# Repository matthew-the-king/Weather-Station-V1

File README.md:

# Weather-Station-V1
The Weather Station V1 is a Solar- and Battery-powered Weather Station that measures humidity, pressure, temperature, and air quality, and sends all data over Wi-Fi for a client to receive or records it to an SD card.

## |FEATURES IN DEPTH|<br>
The Weather Station V1 uses multiple sensors to collect data; here is the list:<br>
1.STS40-AD1B-R3(Temperature Sensor)<br>
2.BMP581(Pressure Sensor)<br>
3.ENS160-BGLT(Air qaulity Sensor)<br>
4.SAM-M10Q-00B(GPS IC)<br>
To view the data the Weather Station V1 collects, the PCB has an SD card slot that records data over long periods and an ESP32-C3 that can send data over WiFi.<br>

<br>
The Weather Station V1 can be powered with a solar panel. To hook up the solar panel, connect the power wires with the correct polarity to the blue screw-in terminal. Here is the [link](https://www.amazon.com/ECO-WORTHY-Monocrystalline-Waterproof-Charging-Applications/dp/B01IFJ73X4/ref=sr_1_4?crid=3QHAHQSNMHFSL&dib=eyJ2IjoiMSJ9.NCFwgk3sAcXWyB454Pk5SPNcQemk34eTFudncpU4z0kJxmG-NXfIaFsG7l4m57yuxXUE0gBqu5lgGJoBbALUTFjF2K6-mGWYJWMwcwzsFfhhP3rzPJ4SUP1idMQb-H-VBpm4El9aRgOr08ZAze0ncVoFDJLv6Px1nW_MmPlfGzO2yde_wccv_r7rToX8MT91kRBLzjtbjo7iDcouW79qZ-3ntSCusWl1HjOpdd0R_DA.tXCmzJyMkYVnmj8B4maCWZT6sQgtKzylotzIh5rUZ2Y&dib_tag=se&keywords=solar%2Bpanels&qid=1789531833&refinements=p_36%3A-3800&rnid=2661611011&sprefix=solar%2Bpanels%2Caps%2C245&sr=8-4&th=1), it cost around $29(As of october 10, 2026), to the Solar panel I am using; any Solar panel that can supply over 2 amps and more than 20 volts will work.<br>
<br>
<br>
The Weather Station V1 features an LTC4162, which is a LiFePO4 battery step-down charger with a Power path. To set up the cell count properly, JP1 and JP4 must be bridged. 
The PCB includes a port for soldering a thermistor for battery protection.

The current configuration of the PCB requires 4 LiFePO4 batteries(https://www.digikey.com/en/products/detail/zeus-battery-products/PCIFR18650-1500/9828824)
The PCB has THT 18650 Battery holder footprint on the bottom side of the board, allowing for quick and easy connection of batteries to the PCB.<br>
<br>
The board has a USB-C port for each MCU to make programming as easy as possible, but in case the user does not want to use USB programming, there are also header pins on the other side of the
board that allow for ESP32 UART programming and STM32 serial wire debug and programming.<br>

<br>
## |PRODUCTION|<br>
To produce the PCB, use your preferred PCB manufacturer (PCBway, JLCPCB, etc.).  The Bill of Materials is listed here:<br>
* If Digi-Key does not have the part stocked, check other vendors like Mouser. <br>
*Prices as of October 10, 2026<br>

| Designator | Footprint | Qty | Value / Part | Part Link |Price|
|---|---|---:|---|---|---|
| BT5 | BAT_BK-18650-PC8 | 1 | BK-18650-PC8 | [Link](https://www.digikey.com/en/products/detail/mpd-memory-protection-devices/BK-18650-PC8/2330515)|$6.22|
| C1 | 0603 | 1 | 330nF | [Link](https://www.digikey.com/en/products/detail/tdk/CGA3E3X7R1H334K080AB/4931465)|$0.26|
| C10, C27, C3, C38, C39, C4, C40, C41, C45, C46, C5, C50, C51, C52, C53, C54, C6, C62, C63, C64, C9 | 0402 | 21 | 0.1uF |[Link](https://www.digikey.com/en/products/detail/samsung-electro-mechanics/CL05A104KA5NNNC/3886701?s=N4IgTCBcDaIMIBkAMBWAggRiQFgNJpQDli4QBdAXyA) | $0.38|
| C11, C37, C44, C57, C65 | 0402 | 5 | 10uF |[Link](https://www.digikey.com/en/products/detail/murata-electronics/GRM155R60J106ME15D/5877401) |$0.85|
| C12, C13, C16, C42, C43, C61, C66 | 0402 | 7 | 1uF |[Link](https://www.digikey.com/en/products/detail/samsung-electro-mechanics/CL05A105KO5NNNC/3886725) |$0.70|
| C14 | 0402 | 1 | 22nF |[Link](https://www.digikey.com/en/products/detail/murata-electronics/GRM155R71H223KA12D/965898) |$0.11|
| C15, C18, C2, C24, C26, C7 | 1210 | 6 | 10uF |[Link](https://www.digikey.com/en/products/detail/murata-electronics/GCJ32EC71H106KA01K/9867929) |$7.08|
| C17, C22, C23, C29, C60, C67, C68, C69 | 0603 | 8 | 0.1uF |[Link](https://www.digikey.com/en/products/detail/kemet/C0603C104K5RACTU/1465594)|$1.12|
| C25, C28 | CAP_EEH-ZA1V151P_PAN | 2 | 150uF |[Link](https://www.digikey.com/en/products/detail/panasonic-industry/EEH-ZA1V151P/3088122) |$3.52|
| C34, C35, C36 | 0805 | 3 | 220nF |[Link](https://www.digikey.com/en/products/detail/kemet/C0805C224K5RACTU/754753) |$0.93|
| C47, C48 | 0201 | 2 | C |Will Post link when Done with testing||
| C49 | 0603 | 1 | 4.7uF |[Link](https://www.digikey.com/en/products/detail/murata-electronics/GRM188R61E475KE11D/3900465) |$0.24|
| C55, C8 | 0603 | 2 | 22uF |[Link](https://www.digikey.com/en/products/detail/holy-stone-enterprise-co-ltd/C0603B226M010T/16895513) |$0.68|
| C56 | WCAP-PSHP_8X8.7_DXL_ | 1 | 470uF |[Link](https://www.digikey.com/en/products/detail/w%C3%BCrth-elektronik/875115252003/5147615) |$1.32|
| C58 | 0402 | 1 | 470pF |[Link](https://www.digikey.com/en/products/detail/murata-electronics/GRM1555C1H471JA01D/587210) |$0.10|
| C59 | 0402 | 1 | 100pF |[Link](https://www.digikey.com/en/products/detail/murata-electronics/GRM1555C1H101JA01D/3693829) |$0.11|
| D1, D5, D6 | D_SOD-123F | 3 | 40V |[Link](https://www.digikey.com/en/products/detail/smc-diode-solutions/DSS14U/8341859) |$0.63|
| D2 | D_SMA | 1 | D |[Link](https://www.digikey.com/en/products/detail/mcc-micro-commercial-components/SK310A-LTP/2642015) |$0.52|
| D3 | D_SOD-123 | 1 | Zener 16V |[Link](https://www.digikey.com/en/products/detail/diodes-incorporated/DDZ9703-7/5218356) |$0.36|
| D4 | D_SMA | 1 | 100V |[Link](https://www.digikey.com/en/products/detail/mcc-micro-commercial-components/SK310A-LTP/2642015) |$0.52|
| ESP32_USB1, STM32_USB1 | SAMESKY_UJ20-C-H-G-SMT-P16-TR | 2 | UJ20-C-H-G-SMT-1-P16-TR |[Link](https://www.digikey.com/en/products/detail/same-sky-formerly-cui-devices/UJ20-C-H-G-SMT-P16-TR/24818595) |$1.30|
| FB1, FB2 | 0603 | 2 | 120R |[Link](https://www.digikey.com/en/products/detail/pulse-electronics/PE-0603PFB121ST/5050544) |$0.20|
| J1 | GCT_MEM2075-00-140-01-A | 1 | MEM2075-00-140-01-A |[Link](https://www.digikey.com/en/products/detail/gct/MEM2075-00-140-01-A/9859614) |$1.92|
| J2 | TE_CONREVSMA002 | 1 | CONREVSMA002 |[Link](https://www.digikey.com/en/products/detail/te-connectivity-linx/CONREVSMA002/340145) |$2.78|
| J3 | PinHeader_1x05_P2.54mm_Vertical | 1 | Conn_01x05_Pin |2.54mm Male Header Pins|
| J4 | PinHeader_1x04_P2.54mm_Vertical | 1 | Conn_01x04_Pin |2.54mm Male Header Pins|
| J5 | OST_OSTTC020162 | 1 | Solar Panel |[Link](https://www.digikey.com/en/products/detail/on-shore-technology-inc/OSTTC020162/614549?s=N4IgTCBcDaIPIGUAqSDCAGM6CMA2CAugL5A) | $0.62|
| JP8, JP9 | PinSocket_1x02_P2.54mm_Vertical | 2 | Jumper_2_Open |2.54mm Male Header Pins|
| L1 | IND_PA4342.402NLT | 1 | 4uH |[Link](https://www.digikey.com/en/products/detail/pulse-electronics/PA4342-402NLT/5641799) |$1.16|
| L2 | 0201 | 1 | L |Will Post link when Done with testing||
| L3 | 1008 | 1 | 1.5uH |[Link](https://www.digikey.com/en/products/detail/murata-electronics/DFE252012P-1R5M-P2/5247259) |$0.22|
| Q10, Q9 | NPNBEC_SOT-23_OSI | 2 | BSR14 |[Link](https://www.digikey.com/en/products/detail/onsemi/BSR14/965251) |$0.96|
| Q11, Q14 | WDFN8_511DR_OSI-L | 2 | FDMC8327L |[Link](https://www.digikey.com/en/products/detail/onsemi/FDMC8327L/4314821?curr=usd&utm_campaign=buynow&utm_medium=aggregator&utm_source=octopart) |$3.00|
| Q3, Q4, Q5, Q6 | TDSON-8-1 | 4 | CSD18534Q5A |[Link](https://www.digikey.com/en/products/detail/texas-instruments/CSD18534Q5A/3830016) |$6.84|
| R1 | 1206 | 1 | 16mΩ |[Link](https://www.digikey.com/en/products/detail/littelfuse-inc/L4CL1206LR016DNR/18795436) |$1.31|
| R10, R11 | 2512 | 2 | 10MΩ |[Link](https://www.digikey.com/en/products/detail/bourns-inc/CHV2512-JW-106ELF/5175992) |$1.02|
| R12, R13, R8, R9 | 0603 | 4 | 330Ω |[Link](https://www.digikey.com/en/products/detail/yageo/RC0603FR-07330RL/727162) |$0.40|
| R14 | 0603 | 1 | 63.4k |[Link](https://www.digikey.com/en/products/detail/yageo/RT0603BRD0763K4L/1072610) |$0.10|
| R15, R16 | 0402 | 2 | 10k |[Link](https://www.digikey.com/en/products/detail/yageo/RC0402JR-0710KL/726418?s=N4IgTCBcDaIEoGEAMAWJYBScC0SDsAjEgNIAyIAugL5A) |$0.11|
| R2, R3, R39, R40 | 0402 | 4 | 4.7kΩ |[Link](https://www.digikey.com/en/products/detail/yageo/RC0402JR-074K7L/726477) |$0.44|
| R20, R25 | 0603 | 2 | 300Ω |[Link](https://www.digikey.com/en/products/detail/yageo/RC0603FR-07300RL/724356) |$0.20|
| R21, R22 | 2512 | 2 | 80.6Ω |[Link](https://www.digikey.com/en/products/detail/koa-speer-electronics-inc/RK73H3ATTE80R6F/10423948) |$0.62|
| R23, R24, R26, R47, R48, R51, R52, R7 | 2010 | 8 | 100Ω |[Link](https://www.digikey.com/en/products/detail/yageo/RT2010FKE07100RL/5945596) |$1.28|
| R27, R28, R29, R30 | 0402 | 4 | 5.1kΩ |[Link](https://www.digikey.com/en/products/detail/yageo/RC0402FR-075K1L/726624?s=N4IgTCBcDaIEoGEAMAWJYBicC0SDsArANICMAMiALoC%2BQA) |$0.40|
| R31, R32, R33, R34, R37, R38, R43, R45, R49 | 0402 | 9 | 10kΩ |[Link](https://www.digikey.com/en/products/detail/yageo/RC0402JR-0710KL/726418?s=N4IgTCBcDaIEoGEAMAWJYBScC0SDsAjEgNIAyIAugL5A) |$0.99|
| R35, R36 | 0402 | 2 | 22Ω |[Link](https://www.digikey.com/en/products/detail/yageo/RC0402FR-0722RL/726562) |$0.22|
| R41 | 0402 | 1 | 100k |[Link](https://www.digikey.com/en/products/detail/yageo/RC0402FR-07100KL/726526) |$0.10|
| R42 | 0402 | 1 | 31.6kΩ |[Link](https://www.digikey.com/en/products/detail/panasonic-industry/ERA-2AEB3162X/2026187) |$0.11|
| R44, R53 | 0402 | 2 | 100kΩ |[Link](https://www.digikey.com/en/products/detail/yageo/RC0402FR-07100KL/726526) |$0.10|
| R46 | MSRSF3920P1L00D2P0 | 1 | 1mΩ |[Link](https://www.digikey.com/en/products/detail/susumu/MSRSF3920P-1L00-D2P0/24396792) |$1.74|
| R50 | 0805 | 1 | 32mΩ |[Link](https://www.digikey.com/en/products/detail/vishay-dale/WSLP0805R0320FEA/9755276) |$1.29|
| S1 | SW_SKRPABE010 | 1 | SKRPABE010 |[Link](https://www.digikey.com/en/products/detail/alps-alpine/SKRPABE010/18768948) |$0.22|
| TH1 | PinHeader_1x02_P1.00mm_Vertical | 1 | 103AT2 |[Link](https://www.digikey.com/en/products/detail/semitec-usa-corp/103AT-2/16579059?s=N4IgTCBcDaIIwAYDMBBAKhAugXyA) |$0.68|
| U1 | UFQFPN-32_STM | 1 | STM32U385KGU6 |[Link](https://www.digikey.com/en/products/detail/stmicroelectronics/STM32U385KGU6/26092104) |$7.31|
| U10 | VQFN20_RGR_TEX | 1 | BQ76907RGRR |[Link](https://www.digikey.com/en/products/detail/texas-instruments/BQ76907RGRR/22077514) |$2.01|
| U11 | SOT-23-5 | 1 | MIC5504-1.8YM5 |[Link](https://www.digikey.com/en/products/detail/microchip-technology/MIC5504-1-8YM5-TR/5209404) |$0.16|
| U12, U13 | PSON50P145X100X60-6N | 2 | TPD4S012DRYR |[Link](https://www.digikey.com/en/products/detail/texas-instruments/TPD4S012DRYR/2037539) |$2.38|
| U14 | IC_MCP16362T-E_NMX | 1 | MCP16362T-E_NMX |[Link](https://www.digikey.com/en/products/detail/microchip-technology/MCP16362T-E-NMXVAO/14291783) |$2.33|
| U2 | QFN10_BMP581_BOS | 1 | BMP581 |[Link](https://www.digikey.com/en/products/detail/bosch-sensortec/BMP581/16036134) |$3.35|
| U3 | STS4X | 1 | STS4X |[Link](https://www.digikey.com/en/products/detail/sensirion-ag/STS40-AD1B-R3/16020549) |$0.72|
| U4 | XDCR_ENS210-LQFM | 1 | ENS210-LQFM |[Link](https://www.digikey.com/en/products/detail/sciosense/ENS210-LQFM/6490747) |$1.62|
| U5 | XDCR_ENS160-BGLT | 1 | ENS160-BGLT |[Link](https://www.digikey.com/en/products/detail/sciosense/ENS160-BGLT/16129831) |$5.72|
| U6 | QFN50P500X500X90-33N | 1 | LTC4162IUFD-FAD_PBF |[Link](https://www.digikey.com/en/products/detail/analog-devices-inc/LTC4162IUFD-FAD-PBF/9446112) |$9.96|
| U7 | XCVR_SAM-M10Q-00B | 1 | SAM-M10Q-00B |[Link](https://www.digikey.com/en/products/detail/u-blox/SAM-M10Q-00B/16672678) |$13.75|
| U8 | QFN50P500X500X90-33N | 1 | ESP32-C3FH4 |[Link](https://www.digikey.com/en/products/detail/espressif-systems/ESP32-C3FH4/14115592) |$2.50|
| Y3 | OSC_ECS-2520S33-400-FN-TR | 1 | 40MHZ |[Link](https://www.digikey.com/en/products/detail/ecs-inc/ECS-2520S33-400-FN-TR/6578428) |$2.25|

Make sure you also purchase an antenna for the RF port; any SMA-Male antenna works. Here is a [link](https://www.digikey.com/en/products/detail/inventek-systems/W24-ASMA-M/4959494) for one.<br>
The total cost of all the PCB components is 135.59 dollars as of right now, with shipping being around an extra $5; when I add the PI filter stuff, it will only go up a dollar max.<br>
I would greatly recommend using a PCB stencil to make soldering components easier, as some of the components are quite small. Remember, in order for the battery functionality to work, JP1 and JP4 must be bridged.<br>
<br>

## |Weather Station Case|<br>
I CAD'd a 3D-printable case for the Weather Station V1 PCB; it has two parts: a front plate and a container part.
There are M.2 threaded insert holes on the container part, so you must purchase threaded inserts and M.2 screws.<br>
<br>

## |Firmware|<br>
So far, I have only added main.cpp, which should be placed in an STM32CubeIDE project.  No code has been written into it yet because I do not have the board to program yet. 

## |Purpose Of Project |<br>
The purpose of the Weather Station V1 was to enhance my understanding of RF applications and battery- and solar-powered devices. Throughout making this project, I understood RF design better and overall PCB design.
I hope this knowledge will allow me to make better, more reliable, and cooler projects in the future.

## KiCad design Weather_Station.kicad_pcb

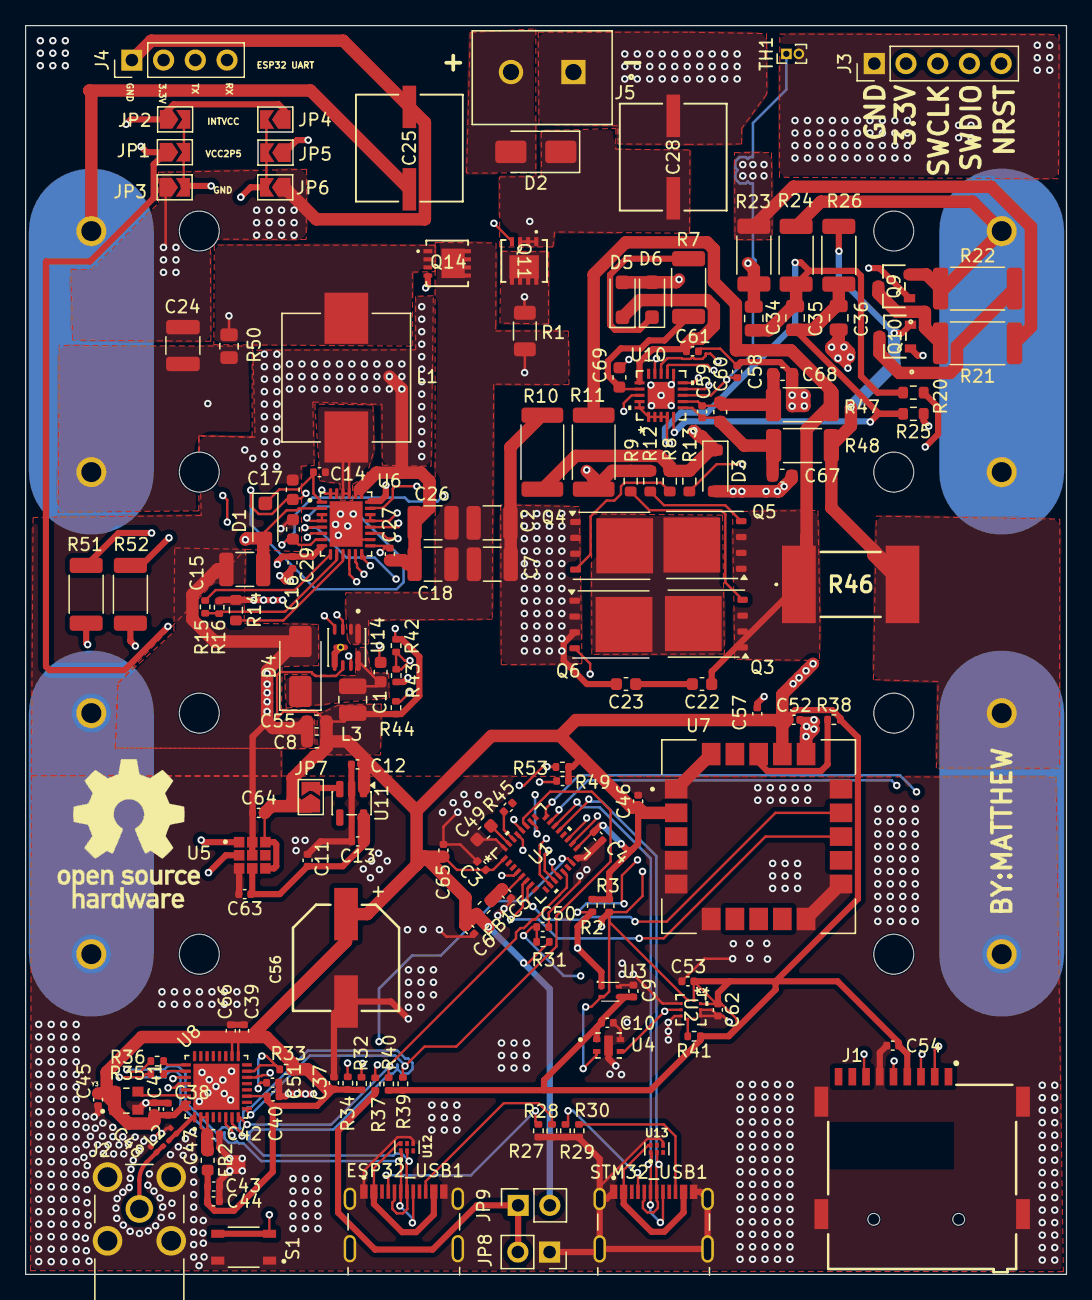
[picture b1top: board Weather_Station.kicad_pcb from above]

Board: 4 copper layers, 83.4 x 100.0 mm, 161 parts (1 on the bottom side), 94 nets.

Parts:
BT5: BK-18650-PC8; BAT_BK-18650-PC8
C1: 330nF; C_0603_1608Metric
C2, C7, C15, C18, C24, C26: 10uF; C_1210_3225Metric
C3, C4, C5, C6, C9, C10, C27, C38, C39, C40, C41, C45, C46, C50, C51, C52, C53, C54, C62, C63, C64: 0.1uF; C_0402_1005Metric
C8, C55: 22uF; C_0603_1608Metric
C11, C37, C44, C57, C65: 10uF; C_0402_1005Metric
C12, C13, C16, C42, C43, C61, C66: 1uF; C_0402_1005Metric
C14: 22nF; C_0402_1005Metric
C17, C22, C23, C29, C60, C67, C68, C69: 0.1uF; C_0603_1608Metric
C25, C28: 150uF; CAP_EEH-ZA1V151P_PAN
C34, C35, C36: 220nF; C_0805_2012Metric
C47, C48: C; C_0201_0603Metric
C49: 4.7uF; C_0603_1608Metric
C56: 470uF; WCAP-PSHP_8X8.7_DXL_
C58: 470pF; C_0402_1005Metric
C59: 100pF; C_0402_1005Metric
D1, D5, D6: 40V; D_SOD-123F
D2: D; D_SMA
D3: Zener 16V; D_SOD-123
D4: 100V; D_SMA
ESP32_USB1: UJ20-C-H-G-SMT-1-P16-TR; SAMESKY_UJ20-C-H-G-SMT-P16-TR
FB1, FB2: 120R; L_0603_1608Metric
J1: MEM2075-00-140-01-A; GCT_MEM2075-00-140-01-A
J2: CONREVSMA002; TE_CONREVSMA002
J3: Conn_01x05_Pin; PinHeader_1x05_P2.54mm_Vertical
J4: Conn_01x04_Pin; PinHeader_1x04_P2.54mm_Vertical
J5: Solar Panel; OST_OSTTC020162
JP1, JP2, JP3, JP4, JP5, JP6, JP7: Jumper_2_Open; SolderJumper-2_P1.3mm_Open_TrianglePad1.0x1.5mm
JP8, JP9: Jumper_2_Open; PinSocket_1x02_P2.54mm_Vertical
L1: 4uH; IND_PA4342.402NLT
L2: L; L_0201_0603Metric
L3: 1.5uH; L_1008_2520Metric
Q3, Q4, Q5, Q6: CSD18534Q5A; TDSON-8-1
Q9, Q10: BSR14; NPNBEC_SOT-23_OSI
Q11, Q14: FDMC8327L; WDFN8_511DR_OSI-L
R1: 16mΩ; R_1206_3216Metric
R2, R3, R39, R40: 4.7kΩ; R_0402_1005Metric
R7, R23, R24, R26, R47, R48, R51, R52: 100Ω; R_2010_5025Metric
R8, R9, R12, R13: 330Ω; R_0603_1608Metric
R10, R11: 10MΩ; R_2512_6332Metric
R14: 63.4k; R_0603_1608Metric
R15, R16: 10k; R_0402_1005Metric
R20, R25: 300Ω; R_0603_1608Metric
R21, R22: 80.6Ω; R_2512_6332Metric
R27, R28, R29, R30: 5.1kΩ; R_0402_1005Metric
R31, R32, R33, R34, R37, R38, R43: 10kΩ; R_0402_1005Metric
R35, R36: 22Ω; R_0402_1005Metric
R41: 100k; R_0402_1005Metric
R42: 31.6kΩ; R_0402_1005Metric
R44, R53: 100kΩ; R_0402_1005Metric
R45, R49: 10kΩ; C_0402_1005Metric
R46: 1mΩ; MSRSF3920P1L00D2P0
R50: 32mΩ; R_0805_2012Metric
S1: SKRPABE010; SW_SKRPABE010
STM32_USB1: UJ20-C-H-G-SMT-1-P16-TR; SAMESKY_UJ20-C-H-G-SMT-P16-TR
TH1: 103AT2; PinHeader_1x02_P1.00mm_Vertical
U1: STM32U385KGU6; UFQFPN-32_STM
U2: BMP581; QFN10_BMP581_BOS
U3: STS4X
U4: ENS210-LQFM; XDCR_ENS210-LQFM
U5: ENS160-BGLT; XDCR_ENS160-BGLT
U6: LTC4162IUFD-FAD_PBF; QFN50P500X400X80-29N
U7: SAM-M10Q-00B; XCVR_SAM-M10Q-00B
U8: ESP32-C3FH4; QFN50P500X500X90-33N
U10: BQ76907RGRR; VQFN20_RGR_TEX
U11: MIC5504-1.8YM5; SOT-23-5
U12, U13: TPD4S012DRYR; PSON50P145X100X60-6N
U14: MCP16362T-E_NMX; IC_MCP16362T-E_NMX
Y3: 40MHZ; OSC_ECS-2520S33-400-FN-TR

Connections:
+1V8: C11.1, C13.1, C63.1, U5.4 (VDD), U11.5 (VOUT)
+3.3V: C3.1, C4.1, C6.1, C8.1, C9.1, C10.1, C12.1, C27.1, C37.1, C38.1, C39.1, C40.1, C41.1, C43.1, C44.1, C45.1, C46.1, C52.1, C53.1, C54.1, C55.1, C56.1, C57.1, C62.1, C64.1, C65.1, C66.1, FB1.2, FB2.2, J1.P4 (VDD), J3.2, J4.2, JP7.1 (A), JP9.2 (B), L3.2, R2.1, R3.2, R31.1, R32.1, R33.2, R34.2, R38.2, R39.1, R40.1, R41.1, R42.1, R44.1, R49.1, R53.1, U1.1 (VDD), U1.17 (VDD), U2.1 (VDDIO), U2.10 (VDD), U3.3 (VDD), U4.1 (VDD), U5.5 (VDDIO), U5.7 (~CS), U6.15 (DVCC), U7.2 (V_IO), U7.17 (VCC), U8.11 (VDD3P3_RTC), U8.17 (VDD3P3_CPU), U8.18 (VDD_SPI), U8.31 (VDDA), U8.32 (VDDA__1), U11.1 (VIN), U14.6 (BD), Y3.1 (TRI_STATE), Y3.4 (VDD)
+BATT: BT5.3+, BT5.4+, C24.1, C25.1, D5.2 (A), D6.2 (A), R21.1, R23.1, R50.2, U6.19 (BATSENS+), U6.20 (CSN)
-BATT: C2.2, C3.2, C4.2, C5.2, C6.2, C7.2, C8.2, C9.2, C10.2, C11.2, C12.2, C13.2, C15.2, C16.2, C17.2, C18.2, C23.2, C24.2, C25.2, C26.2, C27.2, C28.2, C29.2, C36.2, C37.2, C38.2, C39.2, C40.2, C41.2, C42.2, C43.2, C44.2, C45.2, C46.2, C47.2, C48.2, C49.2, C50.2, C51.2, C52.2, C53.2, C54.2, C55.2, C56.2, C57.2, C58.2, C61.1, C62.2, C63.2, C64.2, C65.2, C66.2, C67.2, C68.1, C69.1, D3.2 (A), D4.2 (A), ESP32_USB1.A1_B12 (GND), ESP32_USB1.A12_B1, ESP32_USB1.SH1 (SHIELD), ESP32_USB1.SH2 (SHIELD__1), ESP32_USB1.SH3 (SHIELD__2), ESP32_USB1.SH4 (SHIELD__3), J1.P6 (VSS), J1.SH1 (SHIELD), J1.SH2 (SHIELD__1), J1.SH3 (SHIELD__2), J1.SH4 (SHIELD__3), J2.2, J2.3, J2.4, J2.5, J3.1, J4.1, J5.1, JP3.1 (A), JP6.1 (A), JP8.1 (A), Q4.1 (S), Q4.2 (S), Q4.3 (S), Q6.1 (S), Q6.2 (S), Q6.3 (S), R10.2, R14.2, R16.2, R27.2, R28.2, R29.2, R30.2, R43.2, S1.1, S1.2, STM32_USB1.A1_B12 (GND), STM32_USB1.A12_B1, STM32_USB1.SH1 (SHIELD), STM32_USB1.SH2 (SHIELD__1), STM32_USB1.SH3 (SHIELD__2), STM32_USB1.SH4 (SHIELD__3), TH1.2, U1.16 (VSS), U1.32 (VSS), U2.3 (VSS), U2.5 (SDO), U2.8 (VSS), U2.9 (VSS), U3.4 (VSS), U4.4 (VSS), U4.5 (VSS__1), U5.3 (MISO/ADDR), U5.8 (VSS), U5.9 (VSS__1), U6.16 (SYNC), U6.23 (PGND), U6.24 (PGND__1), U6.29 (AGND), U7.1 (GND), U7.4 (GND__1), U7.5 (GND__2), U7.6 (GND__3), U7.10 (GND__4), U7.11 (GND__5), U7.15 (GND__6), U7.16 (GND__7), U7.20 (GND__8), U8.33 (GND), U10.11 (VSS), U10.21 (EPAD), U11.2 (GND), U12.4 (GND), U13.4 (GND), U14.5 (GND), U14.9 (EP), U14.10, Y3.2 (GND)
/ALERT: R49.2, U1.19 (PA9), U10.14 (ALERT)
/BATFET: Q14.4 (G), U6.22 (BATFET)
/BOOST: C1.1, U14.7 (BOOST)
/BT1+: BT5.1+, BT5.2+, BT5.3-, BT5.4-, Q9.2, R22.1, R24.1
/BT1-: BT5.1-, BT5.2-, Q10.2, R26.1, R46.2, R48.1
/CELLS0: R52.2, U6.17 (CELLS0)
/CELLS1: R51.2, U6.18 (CELLS1)
/CHG: D3.1 (K), R8.1, R10.1, R13.1, U10.10 (CHG)
/CHIP_EN: R37.2, U1.15 (PB1), U8.7 (CHIP_EN)
/CLN: C2.1, C7.1, C17.1, C18.1, C26.1, Q14.5 (D), Q14.6, Q14.7, Q14.8, Q14.9, R1.2, U6.3 (VOUTA), U6.4 (CLN), U6.27 (VOUT), U6.28 (VOUT__1), U14.1 (VIN), U14.2 (EN)
/CLP: Q11.5 (D), R1.1, U6.5 (CLP)
/DSG: R9.2, R11.1, R12.2, U10.9 (DSG)
/ESP32_RX: J4.4, U8.27 (GPIO20/U0RXD)
/ESP32_TX: J4.3, U8.28 (GPIO21/U0TXD)
/ESP_SCL: R40.2, U1.13 (PA7), U8.8 (GPIO3)
/ESP_SDA: R39.2, U1.27 (PB4), U8.9 (GPIO4/MTMS)
/GPIO_9: C51.1, R33.1, S1.3, S1.4, U8.15 (GPIO9)
/GPS_RX: U1.7 (PA1), U7.14 (RXD)
/GPS_TX: U1.6 (PA0), U7.13 (TXD)
/INTVCC: C15.1, D1.2 (A), JP2.1 (A), JP4.1 (A), U6.2 (INTVCC)
/MISO: J1.P7 (DAT0), U1.12 (PA6)
/MOSI: J1.P3 (CMD), U1.28 (PB5)
/NRST: C50.1, J3.5, R31.2, U1.4 (NRST)
/PG: R44.2, U14.4 (PG)
/REGSRC: C61.2, D5.1 (K), U10.16 (REGSRC)
/SCL_1: R3.1, U1.29 (PB6), U2.2 (SCK), U3.2 (SCL), U4.2 (SCL), U5.2 (SCLK/SCL), U6.13 (SCL), U10.12 (SCL)
/SDA_1: R2.2, U1.26 (PB3), U2.4 (SDI), U3.1 (SDA), U4.3 (SDA), U5.1 (MOSI/SDA), U6.14 (SDA), U10.13 (SDA)
/SMBALERT: R53.2, U1.18 (PA8), U6.12 (~SMBALERT)
/SPI_CS: J1.P2 (CD/DAT3), U1.10 (PA4)
/SPI_SCK: J1.P5 (CLK), U1.11 (PA5)
/SRN: C59.1, C60.1, C68.2, R47.2, U10.7 (SRN)
/SRP: C59.2, C60.2, C67.1, R48.2, U10.6 (SRP)
/SWCLK: J3.3, U1.24 (PA14)
/SWDIO: J3.4, U1.23 (PA13)
/TS: C58.1, TH1.1, U10.8 (TS)
/USB_ESP32_DN: ESP32_USB1.A7 (DN1), ESP32_USB1.B7 (DN2), R36.2, U12.2 (D-)
/USB_ESP32_DP: ESP32_USB1.A6 (DP1), ESP32_USB1.B6 (DP2), R35.2, U12.1 (D+)
/USB_STM32_DN: STM32_USB1.A7 (DN1), STM32_USB1.B7 (DN2), U1.21 (PA11), U13.2 (D-)
/USB_STM32_DP: STM32_USB1.A6 (DP1), STM32_USB1.B6 (DP2), U1.22 (PA12), U13.1 (D+)
/VC0: C35.2, C36.1, R25.2, R26.2, U10.5 (VC0)
/VC1: C34.2, C35.1, R20.2, R24.2, U10.1 (VC4), U10.2 (VC3), U10.3 (VC2), U10.4 (VC1), U10.19 (VC6), U10.20 (VC5)
/VC7: C34.1, R23.2, U10.18 (VC7)
/VCC2P5: C16.1, JP1.1 (A), JP5.1 (A), U6.8 (VCC2P5)
/VDD3p3: C42.1, FB2.1, U8.2 (VDD3P3), U8.3 (VDD3P3__1)
unnamed: C22.1, Q3.1 (S), Q3.2 (S), Q3.3 (S), Q5.1 (S), Q5.2 (S), Q5.3 (S), R11.2, R46.1, R47.1
unnamed: C22.2, C23.1
unnamed: C48.1, J2.1, L2.1
unnamed: C14.1, D1.1 (K), U6.1 (BOOST)
unnamed: D2.2 (A), J5.2
unnamed: C28.1, C29.1, D2.1 (K), Q11.1 (S), Q11.2 (S), Q11.3 (S), U6.7 (VIN)
unnamed: C1.2, D4.1 (K), L3.1, U14.8 (SW)
unnamed: D6.1 (K), R7.1
unnamed: ESP32_USB1.A5 (CC1), R27.1
unnamed: ESP32_USB1.B5 (CC2), R28.1
unnamed: ESP32_USB1.A4_B9 (VBUS), ESP32_USB1.A9_B4, U12.6 (VBUS)
unnamed: JP1.2 (B), JP2.2 (B), JP3.2 (B), R52.1
unnamed: JP4.2 (B), JP5.2 (B), JP6.2 (B), R51.1
unnamed: JP7.2 (B), U11.3 (EN)
unnamed: JP8.2 (B), JP9.1 (A), R37.1
unnamed: Q3.5 (D), Q4.5 (D), Q5.5 (D), Q6.5 (D)
unnamed: Q3.4 (G), R9.1
unnamed: Q4.4 (G), R8.2
unnamed: Q5.4 (G), R12.1
unnamed: Q6.4 (G), R13.2
unnamed: Q9.1, R20.1
unnamed: Q9.3, R21.2
unnamed: Q10.1, R25.1
unnamed: Q10.3, R22.2
unnamed: Q11.4 (G), U6.6 (INFET)
unnamed: R29.1, STM32_USB1.A5 (CC1)
unnamed: R30.1, STM32_USB1.B5 (CC2)
unnamed: STM32_USB1.A4_B9 (VBUS), STM32_USB1.A9_B4, U13.6 (VBUS)
unnamed: R45.1, U1.30 (PB7-BOOT0)
unnamed: C49.1, U1.31 (VCAP)
unnamed: C5.1, FB1.1, U1.5 (VDDA)
unnamed: R41.2, U2.6 (CSB)
unnamed: L1.2, Q14.1 (S), Q14.2 (S), Q14.3 (S), R50.1, U6.21 (CSP)
unnamed: R15.2, R16.1, U6.10 (NTC)
unnamed: R15.1, U6.9 (NTCBIAS)
unnamed: R14.1, U6.11 (RT)
unnamed: C14.2, L1.1, U6.25 (SW), U6.26 (SW__1)
unnamed: R38.1, U7.18 (~RESET)
unnamed: R32.2, U8.6 (GPIO2)
unnamed: R34.1, U8.14 (GPIO8)
unnamed: R36.1, U8.25 (GPIO18/USB_D-)
unnamed: R35.1, U8.26 (GPIO19/USB_D+)
unnamed: C47.1, L2.2, U8.1 (LNA_IN)
unnamed: U8.30 (XTAL_P), Y3.3 (OUTPUT)
unnamed: C69.2, R7.2, U10.17 (BAT)
unnamed: R42.2, R43.1, U14.3 (FB)

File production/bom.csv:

Designator,Footprint,Quantity,Value,LCSC Part #
BT5,BAT_BK-18650-PC8,1,BK-18650-PC8,
C1,0603,1,330nF,
"C10, C27, C3, C38, C39, C4, C40, C41, C45, C46, C5, C50, C51, C52, C53, C54, C6, C62, C63, C64, C9",0402,21,0.1uF,
"C11, C37, C44, C57, C65",0402,5,10uF,
"C12, C13, C16, C42, C43, C61, C66",0402,7,1uF,
C14,0402,1,22nF,
"C15, C18, C2, C24, C26, C7",1210,6,10uF,
"C17, C22, C23, C29, C60, C67, C68, C69",0603,8,0.1uF,
"C25, C28",CAP_EEH-ZA1V151P_PAN,2,150uF,
"C34, C35, C36",0805,3,220nF,
"C47, C48",0201,2,C,
C49,0603,1,4.7uF,
"C55, C8",0603,2,22uF,
C56,WCAP-PSHP_8X8.7_DXL_,1,470uF,
C58,0402,1,470pF,
C59,0402,1,100pF,
"D1, D5, D6",D_SOD-123F,3,40V,
D2,D_SMA,1,D,
D3,D_SOD-123,1,Zener 16V,
D4,D_SMA,1,100V,
"ESP32_USB1, STM32_USB1",SAMESKY_UJ20-C-H-G-SMT-P16-TR,2,UJ20-C-H-G-SMT-1-P16-TR,
"FB1, FB2",0603,2,120R,
J1,GCT_MEM2075-00-140-01-A,1,MEM2075-00-140-01-A,
J2,TE_CONREVSMA002,1,CONREVSMA002,
J3,PinHeader_1x05_P2.54mm_Vertical,1,Conn_01x05_Pin,
J4,PinHeader_1x04_P2.54mm_Vertical,1,Conn_01x04_Pin,
J5,OST_OSTTC020162,1,Solar Panel,
"JP1, JP2, JP3, JP4, JP5, JP6, JP7",SolderJumper-2_P1.3mm_Open_TrianglePad1.0x1.5mm,7,Jumper_2_Open,
"JP8, JP9",PinSocket_1x02_P2.54mm_Vertical,2,Jumper_2_Open,
L1,IND_PA4342.402NLT,1,4uH,
L2,0201,1,L,
L3,1008,1,1.5uH,
"Q10, Q9",NPNBEC_SOT-23_OSI,2,BSR14,
"Q11, Q14",WDFN8_511DR_OSI-L,2,FDMC8327L,
"Q3, Q4, Q5, Q6",TDSON-8-1,4,CSD18534Q5A,
R1,1206,1,16mΩ,
"R10, R11",2512,2,10MΩ,
"R12, R13, R8, R9",0603,4,330Ω,
R14,0603,1,63.4k,
"R15, R16",0402,2,10k,
"R2, R3, R39, R40",0402,4,4.7kΩ,
"R20, R25",0603,2,300Ω,
"R21, R22",2512,2,80.6Ω,
"R23, R24, R26, R47, R48, R51, R52, R7",2010,8,100Ω,
"R27, R28, R29, R30",0402,4,5.1kΩ,
"R31, R32, R33, R34, R37, R38, R43, R45, R49",0402,9,10kΩ,
"R35, R36",0402,2,22Ω,
R41,0402,1,100k,
R42,0402,1,31.6kΩ,
"R44, R53",0402,2,100kΩ,
R46,MSRSF3920P1L00D2P0,1,1mΩ,
R50,0805,1,32mΩ,
S1,SW_SKRPABE010,1,SKRPABE010,
TH1,PinHeader_1x02_P1.00mm_Vertical,1,103AT2,
U1,UFQFPN-32_STM,1,STM32U385KGU6,
U10,VQFN20_RGR_TEX,1,BQ76907RGRR,
U11,SOT-23-5,1,MIC5504-1.8YM5,
"U12, U13",PSON50P145X100X60-6N,2,TPD4S012DRYR,
U14,IC_MCP16362T-E_NMX,1,MCP16362T-E_NMX,
U2,QFN10_BMP581_BOS,1,BMP581,
U3,STS4X,1,STS4X,
U4,XDCR_ENS210-LQFM,1,ENS210-LQFM,
U5,XDCR_ENS160-BGLT,1,ENS160-BGLT,
U6,QFN50P500X400X80-29N,1,LTC4162IUFD-FAD_PBF,
U7,XCVR_SAM-M10Q-00B,1,SAM-M10Q-00B,
U8,QFN50P500X500X90-33N,1,ESP32-C3FH4,
Y3,OSC_ECS-2520S33-400-FN-TR,1,40MHZ,
